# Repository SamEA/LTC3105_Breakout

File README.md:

LTC3105_Breakout
================

Energy Harvesting Breakout Board

Link to Datasheet http://www.linear.com/product/LTC3105

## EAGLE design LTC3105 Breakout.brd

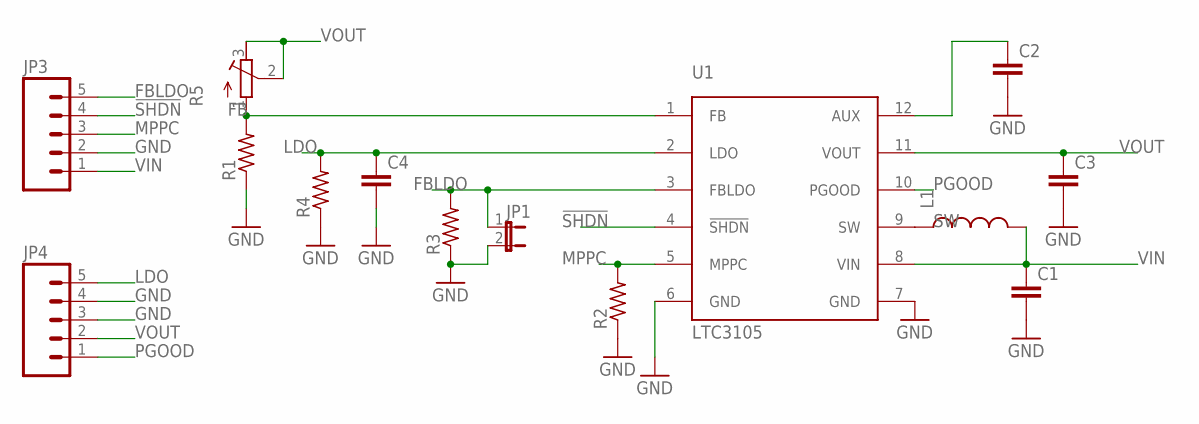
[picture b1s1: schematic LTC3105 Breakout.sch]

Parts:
C1, C3, C4: C-EUC0805; C0805
C2: C-EUC0603; C0603
JP1: JUMPER-2SMD-NO; SJ_2S-NO
JP3, JP4: M05PTH; 1X05
L1: INDUCTOR1210; 1210
R1, R2, R3, R4: R-US_R0603; R0603
R5: R-TRIMM3314J; RTRIM3314J
U1: LTC3105; MSOP

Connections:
!SHDN: JP3.4, U1.4 (!SHDN)
FB: R1.2, R5.1 (E), U1.1 (FB)
FBLDO: JP1.1, JP3.5, R3.2, U1.3 (FBLDO)
GND: C1.2, C2.2, C3.2, C4.2, JP1.2, JP3.2, JP4.3, JP4.4, R1.1, R2.1, R3.1, R4.1, U1.6 (GND), U1.7 (GND)
LDO: C4.1, JP4.5, R4.2, U1.2 (LDO)
MPPC: JP3.3, R2.2, U1.5 (MPPC)
unnamed: C2.1, U1.12 (AUX)
PGOOD: JP4.1, U1.10 (PGOOD)
SW: L1.1, U1.9 (SW)
VIN: C1.1, JP3.1, L1.2, U1.8 (VIN)
VOUT: C3.1, JP4.2, R5.2 (S), R5.3 (A), U1.11 (VOUT)

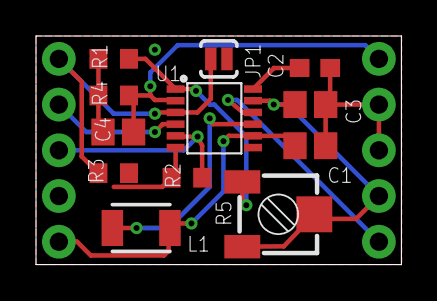
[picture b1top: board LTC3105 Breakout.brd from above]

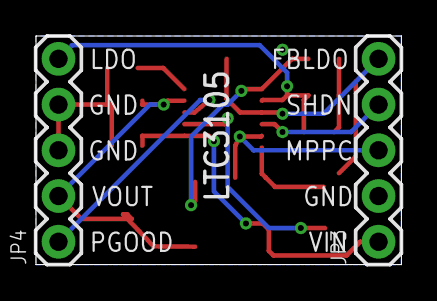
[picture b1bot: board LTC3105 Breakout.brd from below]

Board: 2 copper layers, 20.3 x 12.7 mm, 14 parts (2 on the bottom side), 11 nets.

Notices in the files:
parts and their libraries:
SparkFun-Passives: Licensing: CC v3.0 Share-Alike You are welcome to use this library for commercial purposes.
